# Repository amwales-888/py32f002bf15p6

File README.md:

# py32f002bf15p6
Simple breakout board for py32f002bf15p6 tssop20 24MHz 24kB Flash 2kB Ram 18 IOs MCU

- 3.3v LDO powered from 5V USB.
- UART connectivity to USB via ch340 optionally connected to pins PA6/PA7 using jumpers.
- ARM SWD programming interface header.
- All other pins are broken out to headers.
- 1 LED optionally connected to pin PB4 using jumper.
- 1 Button with pulldown optionally connected to pin PB5 using jumper.
- 1 Button connected to RESET pin, pulled high.

<table>
  <tr>
    <td> </td>
    <td> </td>
  </tr>
  <tr>
    <td> </td>
    <td> </td>
  </tr>
</table>

Resources

<li>https://www.puyasemi.com/en/py32_series.html</li>
<li>https://www.eevblog.com/forum/microcontrollers/$0-11-py32f002a-m0-24mhz-320kb-actually-324kb-more-peripherals/</li>
<li>https://www.cnblogs.com/milton/p/18168592</li>
<li>https://github.com/IOsetting/py32f0-template/tree/main</li>
<li>https://www.cnblogs.com/milton/p/17111286.html</li>
<li>https://www.cnblogs.com/milton/p/18168592</li>
<li>https://www.lcsc.com/product-detail/C7469098.html</li>

<BR>

Notes - The attached firmware was written for the deprecated board produced with EAGLE, since then I have replaced the 
oscillator with a crystal and may have changed the IO pin for LED0/SW0 review the code before using it. I will update 
it when I have time.

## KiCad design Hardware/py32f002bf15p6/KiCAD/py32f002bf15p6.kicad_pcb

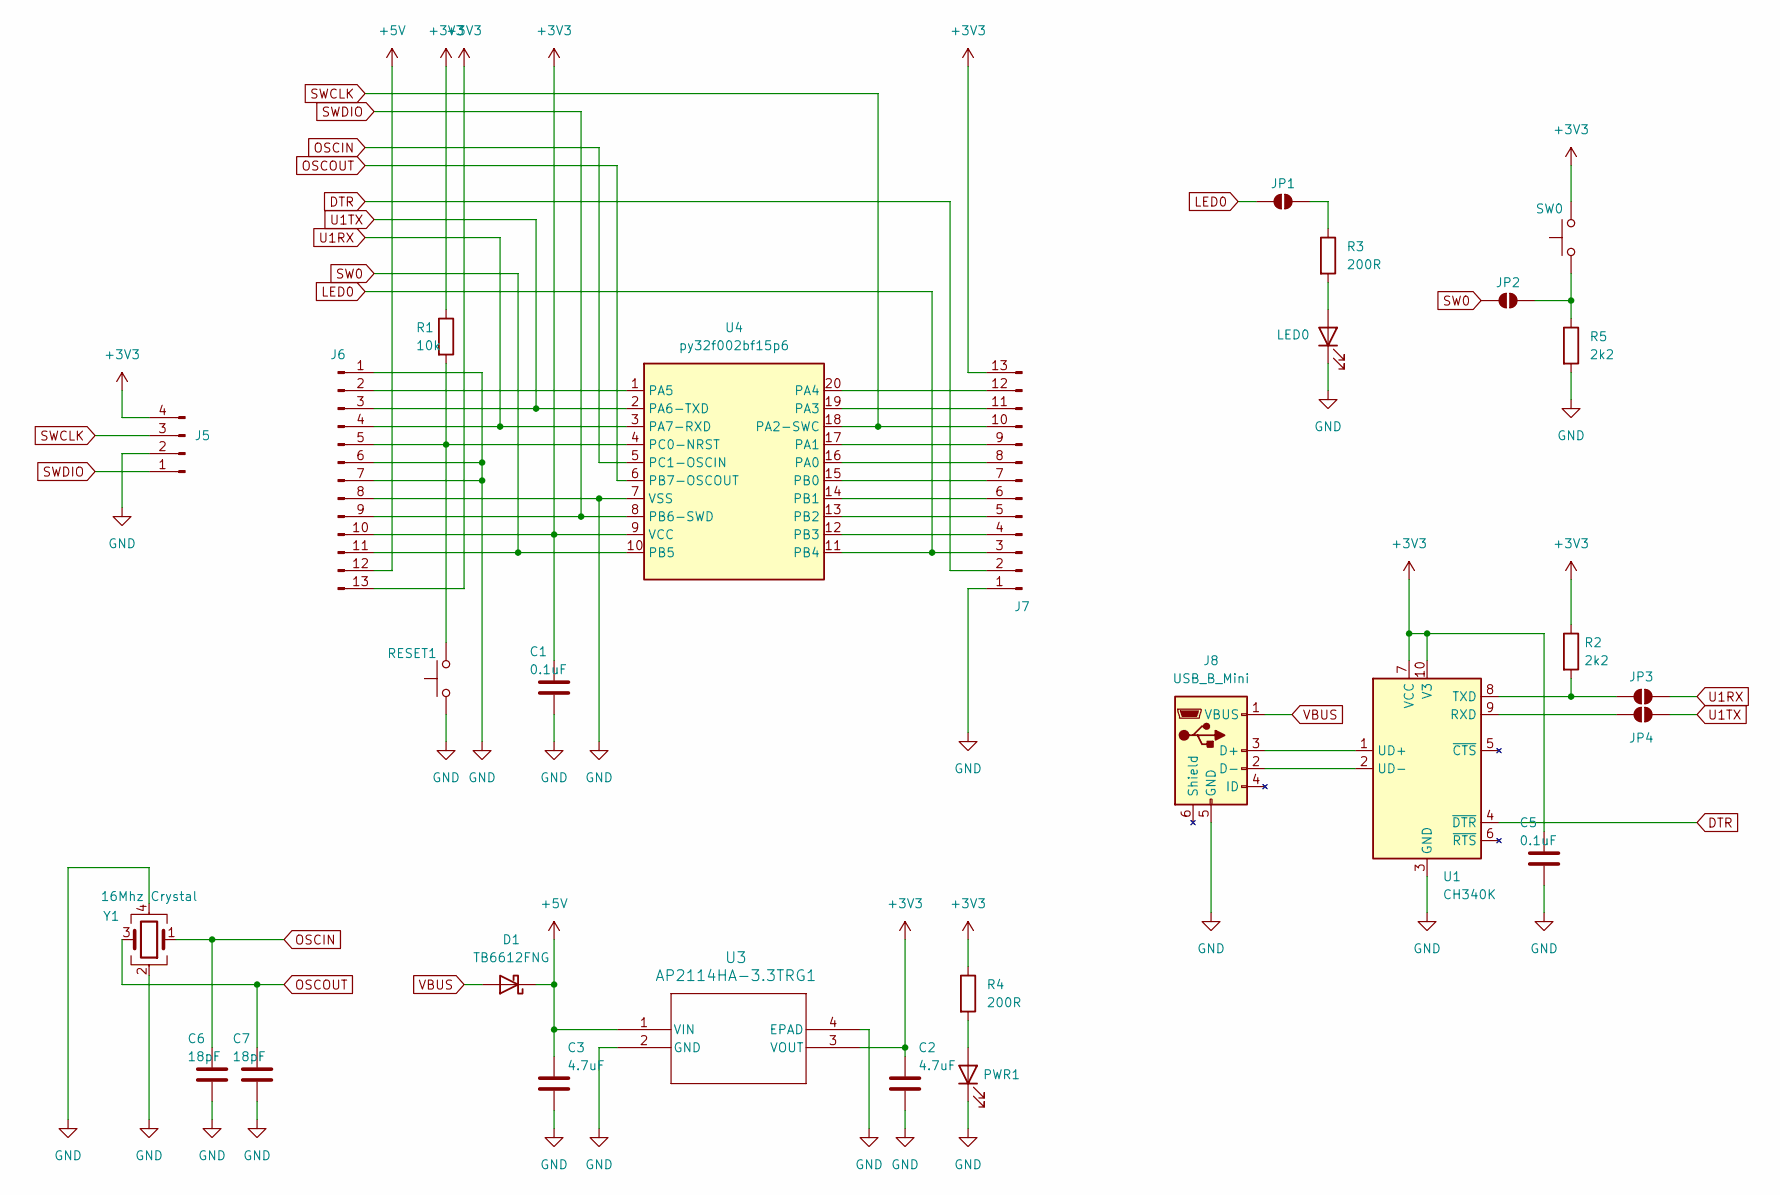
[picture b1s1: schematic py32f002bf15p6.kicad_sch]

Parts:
C1, C5: 0.1uF; C_0805_2012Metric_Pad1.18x1.45mm_HandSolder
C2, C3: 4.7uF; C_1206_3216Metric_Pad1.33x1.80mm_HandSolder
C6, C7: 18pF; C_0603_1608Metric
D1: TB6612FNG; D_SOD-323; LCSC Part# C88224
J5: Conn_01x04_Pin; PinHeader_1x04_P2.54mm_Vertical
J6, J7: Conn_01x13_Pin; PinHeader_1x13_P2.54mm_Vertical
J8: USB_B_Mini; USB_Mini-B_Lumberg_2486_01_Horizontal; LCSC Part# C105424
JP1, JP2, JP3, JP4: SolderJumper_2_Open; SolderJumper-2_P1.3mm_Open_RoundedPad1.0x1.5mm
LED0: LED; LED_0603_1608Metric_Pad1.05x0.95mm_HandSolder
PWR1: LED; LED_0603_1608Metric_Pad1.05x0.95mm_HandSolder
R1: 10k; R_0805_2012Metric_Pad1.20x1.40mm_HandSolder
R2, R5: 2k2; R_0805_2012Metric_Pad1.20x1.40mm_HandSolder
R3, R4: 200R; R_0805_2012Metric_Pad1.20x1.40mm_HandSolder
RESET1: SW_Push; SW_Tactile_SPST_NO_Straight_CK_PTS636Sx25SMTRLFS
SW0: SW_Push; SW_Tactile_SPST_NO_Straight_CK_PTS636Sx25SMTRLFS
U1: CH340K; SSOP-10-1EP_3.9x4.9mm_P1mm_EP2.1x3.3mm; LCSC Part# C968586
U3: AP2114HA-3.3TRG1; SOT-223_DIO; LCSC Part# C460314
U4: py32f002bf15p6; TSSOP-20_4.4x6.5mm_P0.65mm; LCSC Part# C3018715
Y1: 16Mhz Crystal; CDFN-4_2.5x3.2mm_P2.1mm; LCSC Part# C41383242

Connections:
+3V3: C1.1, C2.1, C5.1, J5.4, J6.10, J6.13, J7.13, R1.1, R2.1, R4.1, SW0.2, U1.7 (VCC), U1.10 (V3), U3.3 (VOUT), U4.9 (VCC)
+5V: C3.1, D1.1 (K), J6.12, U3.1 (VIN)
DTR: J7.2, U1.4 (~DTR)
GND: C1.2, C2.2, C3.2, C5.2, C6.2, C7.2, J5.2, J6.1, J6.6, J6.7, J6.8, J7.1, J8.5 (GND), LED0.1 (K), PWR1.1 (K), R5.2, RESET1.1, U1.3 (GND), U3.2 (GND), U3.4 (EPAD), U4.7 (VSS), Y1.2, Y1.4
LED0: J7.3, JP1.1 (A), U4.11 (PB4)
unnamed: J6.2, U4.1 (PA5)
unnamed: J6.5, R1.2, RESET1.2, U4.4 (PC0-NRST)
unnamed: J7.4, U4.12 (PB3)
unnamed: J7.5, U4.13 (PB2)
unnamed: J7.6, U4.14 (PB1)
unnamed: J7.7, U4.15 (PB0)
unnamed: J7.8, U4.16 (PA0)
unnamed: J7.9, U4.17 (PA1)
unnamed: J7.11, U4.19 (PA3)
unnamed: J7.12, U4.20 (PA4)
unnamed: J8.3 (D+), U1.1 (UD+)
unnamed: J8.2 (D-), U1.2 (UD-)
unnamed: JP1.2 (B), R3.1
unnamed: JP2.2 (B), R5.1, SW0.1
unnamed: JP3.1 (A), R2.2, U1.8 (TXD)
unnamed: JP4.1 (A), U1.9 (RXD)
unnamed: LED0.2 (A), R3.2
unnamed: PWR1.2 (A), R4.2
OSCIN: C6.1, U4.5 (PC1-OSCIN), Y1.1
OSCOUT: C7.1, U4.6 (PB7-OSCOUT), Y1.3
SW0: J6.11, JP2.1 (A), U4.10 (PB5)
SWCLK: J5.3, J7.10, U4.18 (PA2-SWC)
SWDIO: J5.1, J6.9, U4.8 (PB6-SWD)
U1RX: J6.4, JP3.2 (B), U4.3 (PA7-RXD)
U1TX: J6.3, JP4.2 (B), U4.2 (PA6-TXD)
VBUS: D1.2 (A), J8.1 (VBUS)

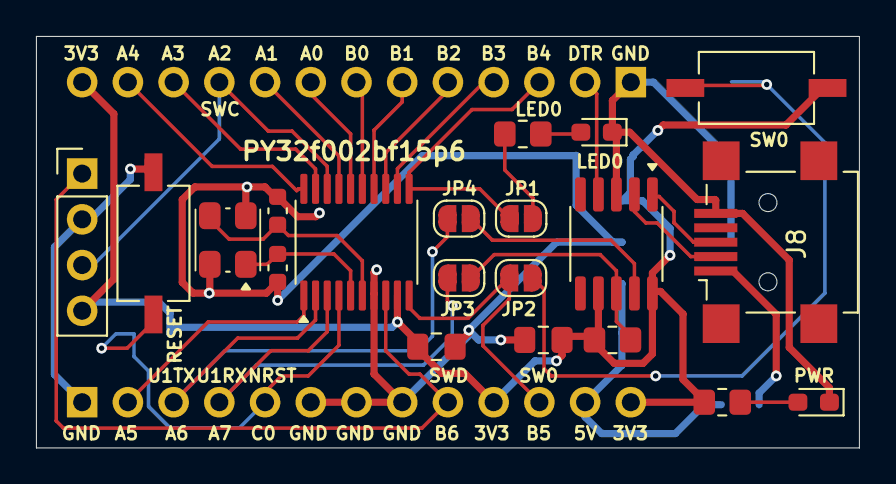
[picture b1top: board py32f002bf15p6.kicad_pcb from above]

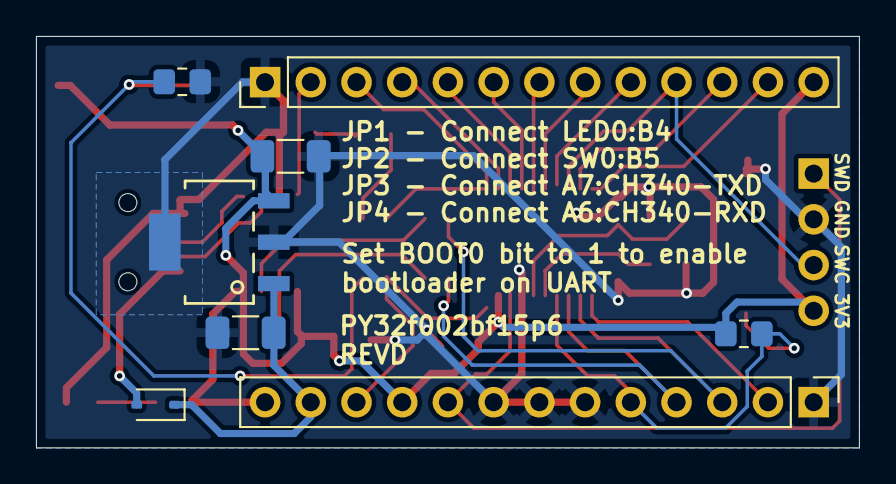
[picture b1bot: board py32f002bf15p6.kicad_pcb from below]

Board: 2 copper layers, 45.7 x 22.9 mm, 28 parts (8 on the bottom side), 31 nets.

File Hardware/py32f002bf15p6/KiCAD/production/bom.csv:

Designator,Footprint,Quantity,Value,LCSC Part #
"C1, C5",0805,2,0.1uF,
"C2, C3",1206,2,4.7uF,
"C6, C7",0603,2,18pF,
D1,D_SOD-323,1,TB6612FNG,
J5,PinHeader_1x04_P2.54mm_Vertical,1,Conn_01x04_Pin,
"J6, J7",PinHeader_1x13_P2.54mm_Vertical,2,Conn_01x13_Pin,
J8,USB_Mini-B_Lumberg_2486_01_Horizontal,1,USB_B_Mini,
"LED0, PWR1",0603,2,LED,
R1,0805,1,10k,
"R2, R5",0805,2,2k2,
"R3, R4",0805,2,200R,
"RESET1, SW0",SW_Tactile_SPST_NO_Straight_CK_PTS636Sx25SMTRLFS,2,SW_Push,
U1,SSOP-10-1EP_3.9x4.9mm_P1mm_EP2.1x3.3mm,1,CH340K,
U3,SOT-223_DIO,1,AP2114HA-3.3TRG1,
U4,TSSOP-20_4.4x6.5mm_P0.65mm,1,py32f002bf15p6,
Y1,CDFN-4_2.5x3.2mm_P2.1mm,1,16Mhz Crystal,

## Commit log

2024-08-14 Initial Checkin
2024-08-31 Final Draft
2024-09-03 Looks likes I screwed up UART TX/RX pins
    Looks likes I screwed up UART TX/RX pins - im blaming submitting the board after returning from holiday before rechecking
2024-09-10 Ensure button is pulled down
    Ensure button is pulled down
2024-09-13 Added simple demo that toggles LED and send output to serial at 9600,8,n,1 through attached USB/Serial interface chip
2024-09-13 Generate final gerbers and rename directories to match chip name
2024-09-13 remove old file
2024-09-20 Replaced 4.7uf 0805 caps for larger 1206 parts
2024-09-27 Updated silkscreen, removed reset header pin
2024-09-29 Rename directories to match other py32 project
2026-04-24 Reformat Directory Structure and Add KiCAD version
    Reformat Directory Structure and Add KiCAD version
2026-04-24 Update README with corrected pin connections and images
2026-04-24 Change silkscreen and update gerbers
2026-04-24 Deprecated old eagle layout
    Deprecated old eagle layout
2026-04-25 Update README with new resource links
    Added additional resources for the py32 series.
2026-04-25 Update README with firmware notes
    Added notes about firmware compatibility and changes.
2026-04-25 Add LCSC product link to README
    Added a new link to LCSC product detail in the README.
